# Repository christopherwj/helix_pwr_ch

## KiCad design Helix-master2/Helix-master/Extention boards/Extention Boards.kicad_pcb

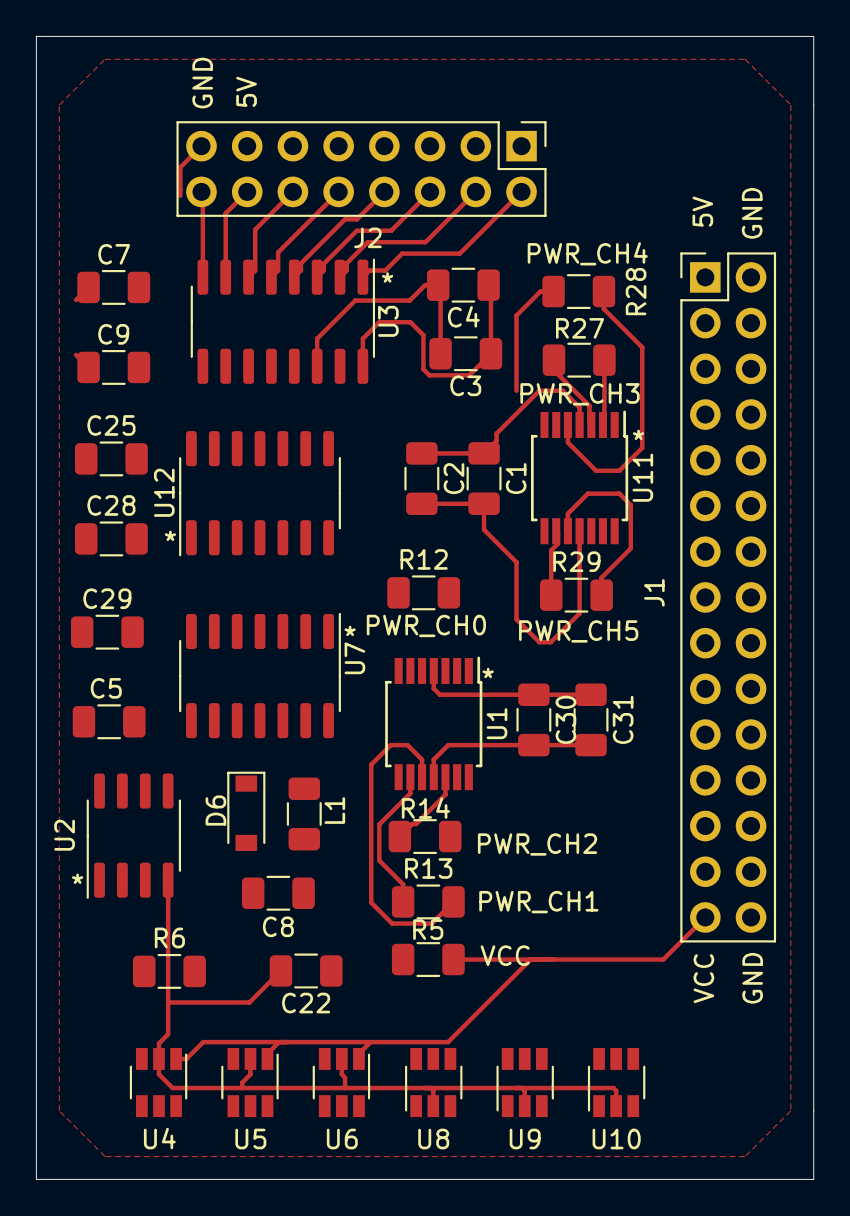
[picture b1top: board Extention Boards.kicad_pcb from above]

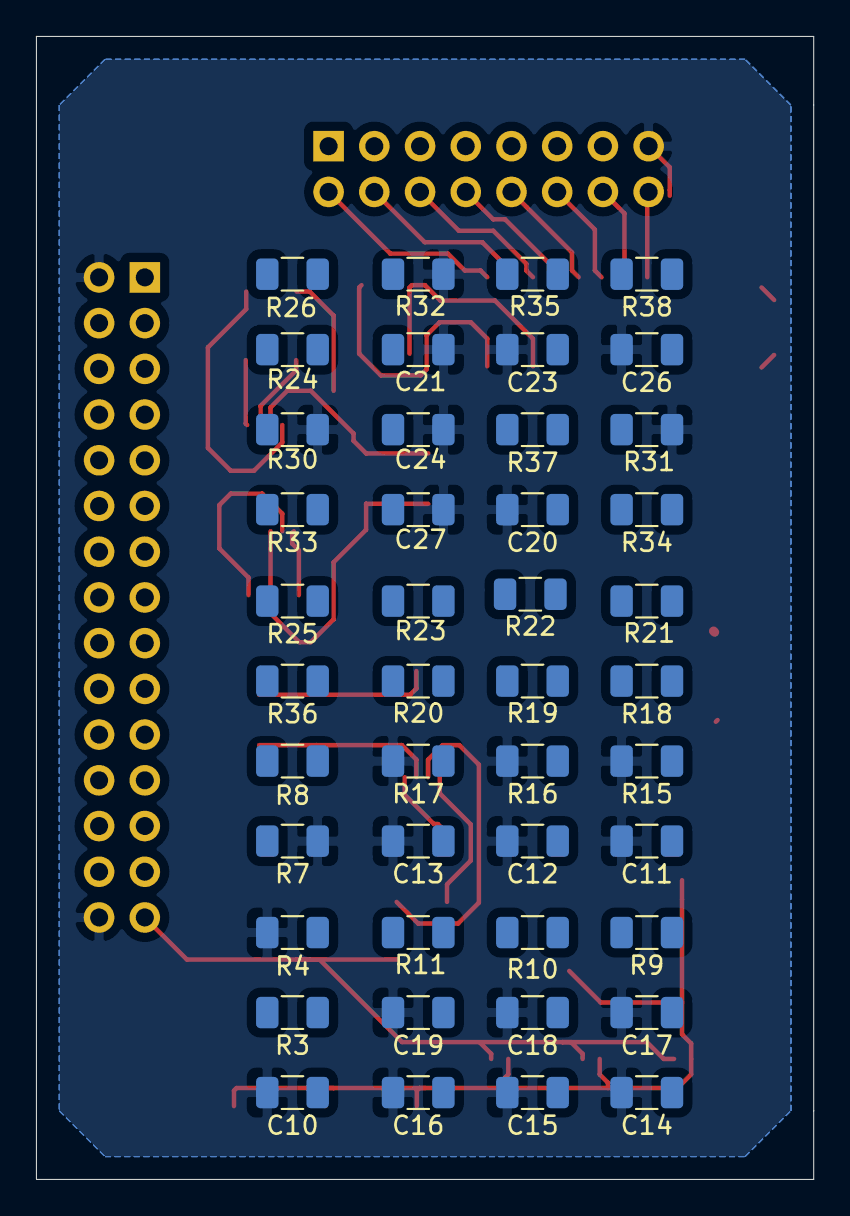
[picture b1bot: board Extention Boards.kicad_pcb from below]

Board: 2 copper layers, 43.2 x 63.5 mm, 82 parts (44 on the bottom side), 62 nets.

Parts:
C1, C3, C5, C7, C11, C12, C13, C20, C21, C22, C30: 10uF; C_1206_3216Metric
C2, C4, C9, C17, C18, C19, C26, C27, C28, C29, C31: .1uF; C_1206_3216Metric
C8: 180pF; C_1206_3216Metric
C10: 100uF; C_1206_3216Metric
C14, C15, C16, C23, C24, C25: 6.8nF; C_1206_3216Metric
D6: 1N5819; D_SOD-123
J1: Conn_02x15_Odd_Even; PinHeader_2x15_P2.54mm_Vertical
J2: Conn_02x08_Odd_Even; PinHeader_2x08_P2.54mm_Vertical
L1: 47uH; L_1206_3216Metric
R3, R8: 27k; R_1206_3216Metric
R4, R7: 9k; R_1206_3216Metric
R5, R6, R12, R13, R14, R27, R28, R29: .5; R_1206_3216Metric
R9, R10, R11, R24, R25, R26: 680; R_1206_3216Metric
R15, R16, R17, R18, R19, R20, R21, R22, R23, R30, R31, R32, R33, R34, R35, R36, R37, R38: 4.7k; R_1206_3216Metric
U1, U11: INA4180; TSSOP-14_4.4x5mm_P0.65mm
U2: MC33063; SOIC-8_3.9x4.9mm_P1.27mm
U3: MCP3008; SOIC-16_3.9x9.9mm_P1.27mm
U4, U5, U6, U8, U9, U10: TPS22810; TSOT-23-6
U7, U12: LM339; SOIC-14_3.9x8.7mm_P1.27mm

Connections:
+5V: C1.1, C2.1, C3.1, C4.1, C5.1, C7.1, C9.1, C10.1, C20.1, C21.1, C22.1, C29.1, C30.1, C31.1, J1.1, J1.5, J1.11, J1.16, J1.17, J1.22, J1.23, J2.13, L1.2, R8.2, R18.1, R19.1, R20.1, R33.1, R34.1, R35.1, U1.4, U3.15, U3.16, U7.3, U8.1, U9.1, U10.1, U11.4, U12.3
GND: C1.2, C2.2, C3.2, C4.2, C5.2, C7.2, C8.2, C9.2, C10.2, C11.2, C12.2, C13.2, C14.2, C15.2, C16.2, C17.2, C18.2, C19.2, C20.2, C21.2, C22.2, C23.2, C24.2, C25.2, C26.2, C27.2, C28.2, C29.2, C30.2, C31.2, D6.2, J1.2, J1.30, J2.15, R4.2, R7.1, R15.2, R16.2, R17.2, R30.2, R31.2, R32.2, U1.11, U2.4, U3.9, U3.14, U4.2, U5.2, U6.2, U7.12, U8.2, U9.2, U10.2, U11.11, U12.12
MCP_CLK: J1.4, U3.13
MCP_CS: J1.10, U3.10
MCP_D_IN: J1.8, U3.11
MCP_D_OUT: J1.6, U3.12
unnamed: C8.1, U2.3
unnamed: C14.1, U4.4
unnamed: C15.1, U5.4
unnamed: C16.1, U6.4
unnamed: C17.1, R9.1, R12.2, U1.5, U4.6
unnamed: C18.1, R10.1, R13.2, U1.10, U5.6
unnamed: C19.1, R11.1, R14.2, U1.12, U6.6
unnamed: C23.1, U8.4
unnamed: C24.1, U9.4
unnamed: C25.1, U10.4
unnamed: C26.1, R24.1, R27.2, U8.6, U11.3
unnamed: C27.1, R25.1, R28.2, U9.6, U11.5
unnamed: C28.1, R26.1, R29.2, U10.6, U11.10
unnamed: D6.1, L1.1, U2.2
unnamed: R5.2, R6.1, U1.2, U2.1, U2.6, U2.8
unnamed: R6.2, U2.7
unnamed: R7.2, R8.1, U2.5
unnamed: R9.2, U4.5
unnamed: R10.2, U5.5
unnamed: R11.2, U6.5
unnamed: R15.1, R18.2, R21.2, U7.5
unnamed: R16.1, R19.2, R22.2, U7.7
unnamed: R17.1, R20.2, R23.2, U7.11
unnamed: R24.2, U8.5
unnamed: R25.2, U9.5
unnamed: R26.2, U10.5
unnamed: R30.1, R33.2, R36.2, U7.9
unnamed: R31.1, R34.2, R37.2, U12.5
unnamed: R32.1, R35.2, R38.2, U12.7
PWR_CH0_CURR_OVLD: J1.7, R21.1, U7.2
PWR_CH0_CURR_SENS: J2.6, U1.7, U3.3, U7.4
PWR_CH0_EN: J1.3, U4.3
PWR_CH0_OUT: J2.1, R12.1, U1.6
PWR_CH1_CURR_OVLD: J1.13, R22.1, U7.1
PWR_CH1_CURR_SENS: J2.8, U1.8, U3.4, U7.6
PWR_CH1_EN: J1.9, U5.3
PWR_CH1_OUT: J2.3, R13.1, U1.9
PWR_CH2_CURR_OVLD: J1.19, R23.1, U7.13
PWR_CH2_CURR_SENS: J2.10, U1.14, U3.5, U7.10
PWR_CH2_EN: J1.15, U6.3
PWR_CH2_OUT: J2.5, R14.1, U1.13
PWR_CH3_CURR_OVLD: J1.25, R36.1, U7.14
PWR_CH3_CURR_SENS: J2.12, U3.6, U7.8, U11.1
PWR_CH3_EN: J1.21, U8.3
PWR_CH3_OUT: J2.7, R27.1, U11.2
PWR_CH4_CURR_OVLD: J1.18, R37.1, U12.2
PWR_CH4_CURR_SENS: J2.14, U3.7, U11.7, U12.4
PWR_CH4_EN: J1.14, U9.3
PWR_CH4_OUT: J2.9, R28.1, U11.6
PWR_CH5_CURR_OVLD: J1.24, R38.1, U12.1
PWR_CH5_CURR_SENS: J2.16, U3.8, U11.8, U12.6
PWR_CH5_EN: J1.20, U10.3
PWR_CH5_OUT: J2.11, R29.1, U11.9
VCC: C11.1, C12.1, C13.1, J1.29, R3.1, R5.1, U1.3, U4.1, U5.1, U6.1
VCC_CURR_SENS: J2.4, U1.1, U3.2
VCC_SENS: J2.2, R3.2, R4.1, U3.1

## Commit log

2019-09-15 Progressed up to routing the board
    Still needs:
    m4 x4 stand offs
    trace routing on front and back.
    documenation for pinout
    5v versus Vcc on PWR_CHx's CH0-2 use VCC whereas PWR_CH3-5 use 5V.
2019-09-23 Tracing and mounting holes left to do
    still left to do:
    M4 mounting holes.
    traces for top and bottom layers
    vias to connect bottom components
    board silkscreen identifiers
    "Pwr_curr_sens"
